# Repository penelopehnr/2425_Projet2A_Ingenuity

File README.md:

# 2425_Projet2A_Ingenuity

**Students :**

- Pénélope HENNER - penelope.henner@ensea.fr
- Kavin DUGARD - kevin.dugard@ensea.fr 
- Elio FLANDIN - elio.flandin@ensea.fr
- Joel COLASO - joel.colaso@ensea.fr

## Project background:

Mars 2020 is a space mission to deploy the Perseverance rover on the Martian surface to study its surface and collect soil samples. It is the first of a series of three missions whose ultimate aim is to return these samples to Earth for analysis.

Ingenuity is a small helicopter developed by NASA, the US space agency. It is being used experimentally on the surface of Mars during the Mars 2020 mission. The helicopter is on board the Perseverance rover.

On April 19, 2021, for the first time in the history of the space age, a spacecraft makes a powered flight through the tenuous atmosphere of another planet. Ingenuity's objective is optical reconnaissance of the terrain, with the helicopter taking numerous aerial photos used by the pilots of the Perseverance astromobile to identify obstacles and promising sites (taking rock samples from the Martian soil).

Ingenuity is a 1.8 kg helicopter with 2 coaxial counter-rotating rotors. It draws its energy from 6 lithium-ion batteries recharged by solar cells. Its navigation system enables it to follow a pre-programmed route without human intervention. Its only payload is a camera.

The mission recently came to an end (January 18, 2024) when a blade broke during the 72nd flight.

Ingenuity has opened up new prospects for Mars exploration. NASA and ESA, as part of their Mars sample return mission, are now including 2 similar helicopters to collect the tubes containing the Martian samples deposited by the Perseverance astromobile in the event of its failure.

 Our project is therefore to try to build the Ingenuity module in miniature. In other words, we want to create a vehicle that can move through the air and take a photo of what's going on below.

 [Learn more about the Mars 2020 mission](Ingenuity%20March%202020.md)

## Our project

Our project is to try and make this helicopter in miniature mode. In other words, we want to create a vehicle that can move through the air and take a photo of what's happening below. To do this, we'll have a total of 10 sessions in which we'll have to mix PCBs, coding, soldering and so on.

## Project architecture

## Description of repo structure:

``````
.
├── Assets/            # Project images (drone, PCB)
├── Datasheets/        # Component datasheets
├── Hardware/          # Architecture diagrams, KiCad (PCB) files and 3D files
├── Software/          # Embedded code (STM32) + Python code + TOF module
├── README.md          # Main project documentation
├── Ingenuity March 2020.md  # Background on the Mars 2020 mission

``````

In the **Assets** folder, you will find pictures of the drone and the assembled PCB.

The **Datasheets** folder contains documentation for all the components we used throughout the project.

The **Hardware** folder includes all the KiCad files needed to reproduce our custom PCB, along with the Bill of Materials (BOM) listing all components, their references, and specifications. You will also find files for 3D printing and laser cutting the various structural parts of the drone.

The **Software** folder contains:
- The **Python code** used to build the graphical user interface (GUI) on the PC to communicate with the Raspberry Pi (`Client_GUI.py`).
- The **Python code** running on the Raspberry Pi, which handles communication with the microcontroller and takes pictures (`server.py`).
- The **TOF code** (developed with STM32CubeIDE), which is responsible for sending the drone’s altitude using a Time-of-Flight sensor.
- The **C code** (also under STM32CubeIDE) in `Ingenuity_2A`, running on the STM32 microcontroller, which receives commands from the Raspberry Pi and manages the components such as motors, TOF sensor, etc.

## Environments used: 

### Machines Used
- **PC (Windows/macOS/Linux)**: Used for development (STM32CubeIDE, Python, OnShape, etc.).
- **Function Generator (GBF)**: Used to simulate control signals during motor testing.
- **Laser Cutter (FabLab)**: Used to cut the wooden drone structure.

### Hardware
- **Raspberry Pi Zero**: A single-board computer used for image capture, PCB interfacing, and running Python scripts.
- **STM32L412KBT6**: Main microcontroller used on the custom PCB.
- **VL53L1X**: Time-of-Flight (ToF) distance sensor.
- **ESC (Electronic Speed Controllers)**: To control brushless motors.
- **Brushless Motors**: Used to generate drone thrust.
- **LDO BU33TD3WG**: Low-dropout voltage regulator.
- **Buck Converter 17395xx36**: DC-DC converter used to step down voltage.
- **MOSFETs**: Used for power switching and motor control.
- **Camera (connected to Raspberry Pi)**: Captures aerial images.

### Software
#### Embedded Development
- **STM32CubeIDE**: Used to write, compile, and flash firmware to the microcontroller.
- **STM32 HAL Drivers**: Low-level drivers for managing STM32 peripherals.

#### Electronic Design
- **KiCad**: Used for circuit schematic design, PCB layout, and Gerber/BOM export.
- **OnShape**: Used for 3D modeling of the drone structure.

#### Python Development
- **Python 3**: Used for drone communication scripts and the graphical user interface (GUI).
- **Tkinter / PyQt**: Used to build the GUI interface.
- **Pygame / Other sound libraries**: For playing feedback sounds (from the `sounds/` folder).
- **Flask / TCP Sockets**: For communication between the GUI and the drone.

## Precision on the TOF VL53L1X

Start by copying the ```VL53L1X_ULD_API``` in your project. You want to configure the paths in your IDE (eg. in STM32CubeIDE : ```Project > Properties``` then ```C/C++ General > Paths and Symbols```).

Source (code and explanations): https://github.com/lfiack/tof_VL53L1X-SATEL/blob/main/README.md

## Precise notice of our project 

[Mini-Ingenuity notice](Mini-Ingenuity_notice.md)

## Logbook

[Logbook](LogBook.md)

## Picture of Mini-Ingenuity

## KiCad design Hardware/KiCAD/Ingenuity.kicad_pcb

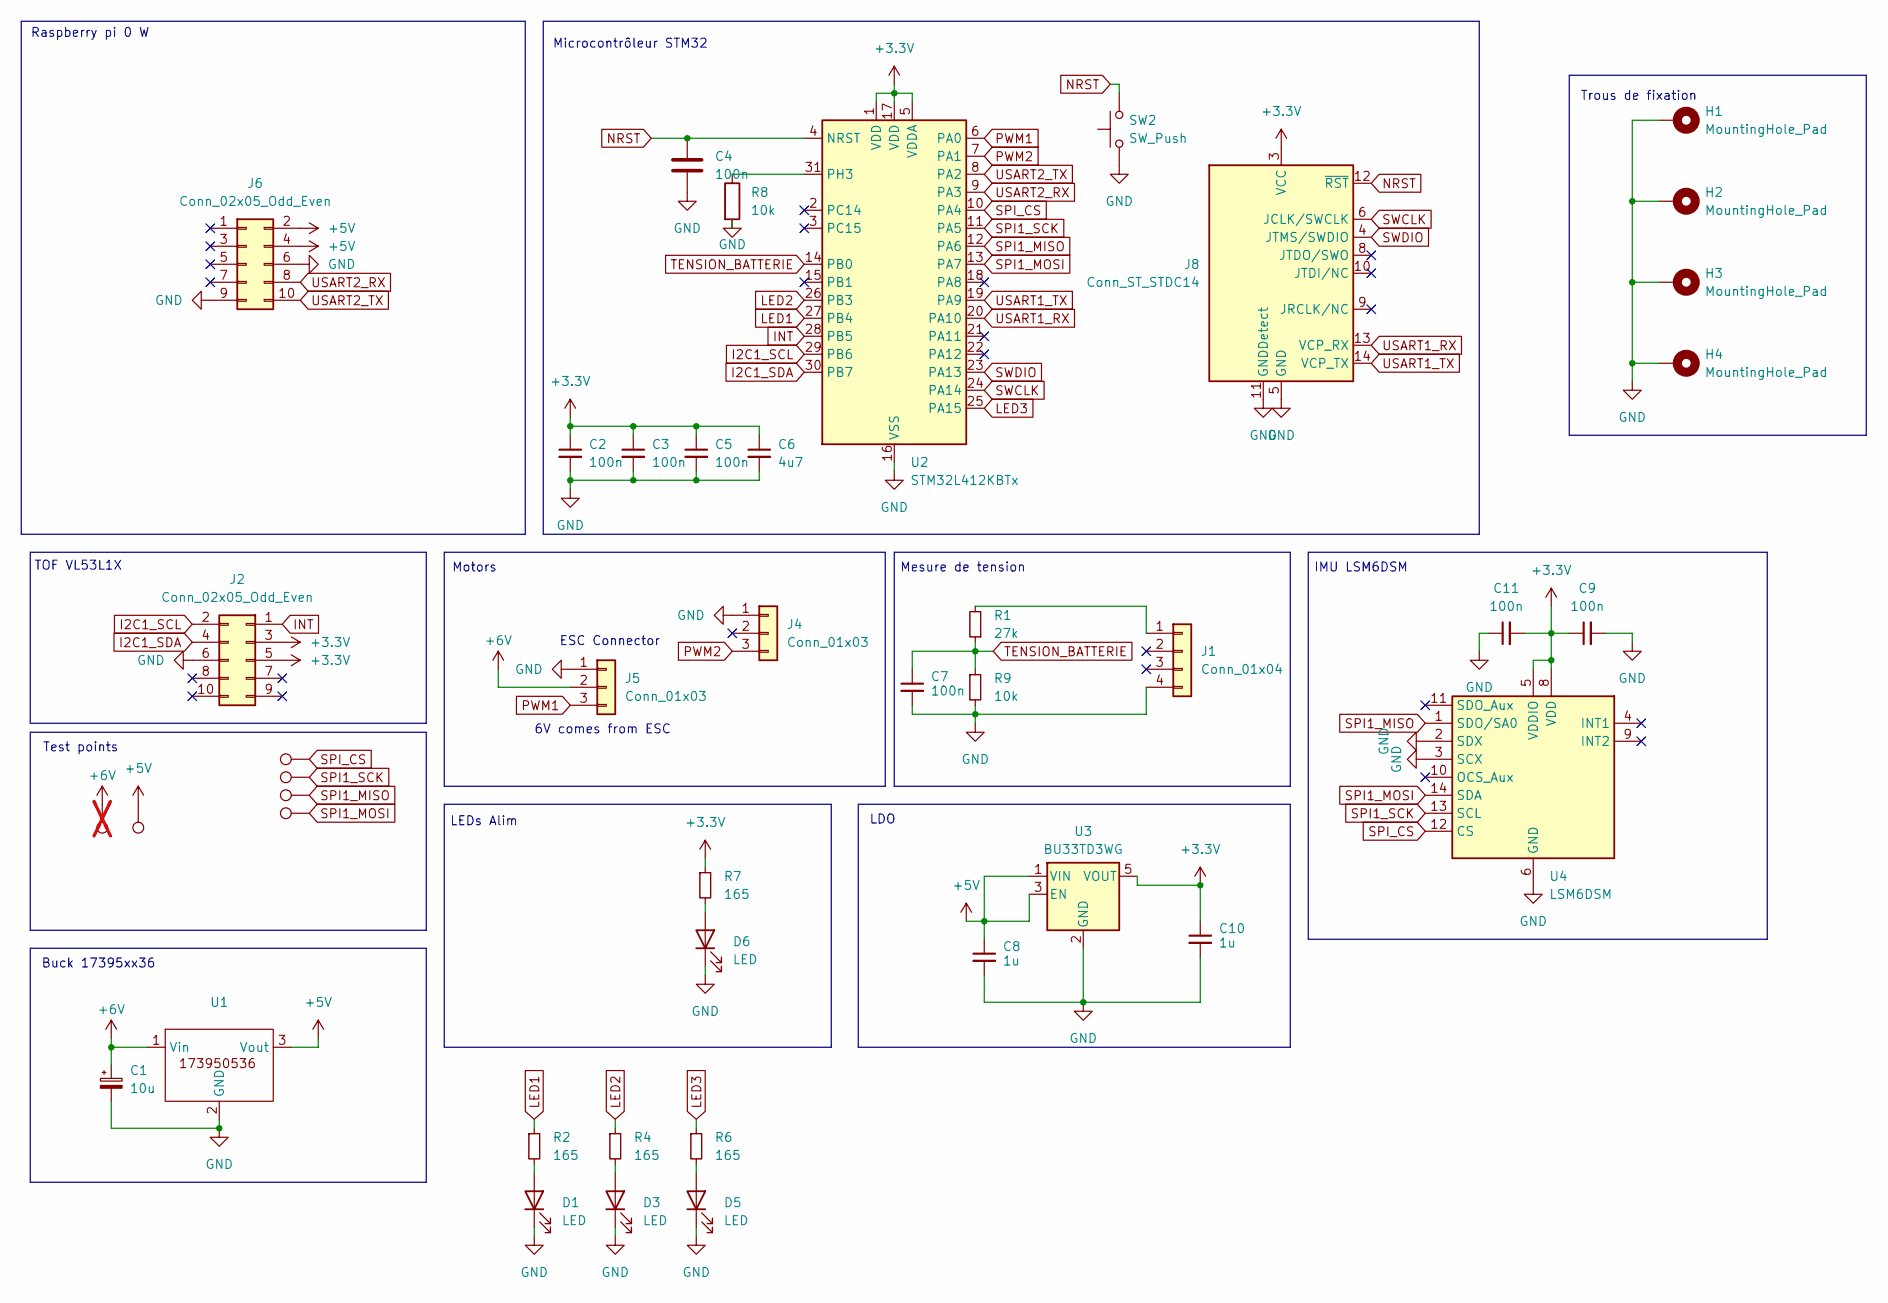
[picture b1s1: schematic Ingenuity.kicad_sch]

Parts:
C1: 10u; C_0603_1608Metric
C2, C3, C4, C5, C7, C9, C11: 100n; C_0402_1005Metric
C6: 4u7; C_0402_1005Metric
C8, C10: 1u; C_0402_1005Metric
D1, D3, D5, D6: LED; LED_0603_1608Metric
H1, H2, H3, H4: MountingHole_Pad; MountingHole_2.7mm_M2.5_DIN965_Pad
J1: Conn_01x04; JST_XH_B4B-XH-A_1x04_P2.50mm_Vertical
J2, J6: Conn_02x05_Odd_Even; PinHeader_2x05_P2.54mm_Vertical
J4, J5: Conn_01x03; JST_XH_B3B-XH-A_1x03_P2.50mm_Vertical
J8: Conn_ST_STDC14; PinHeader_2x07_P1.27mm_Vertical_SMD
R1: 27k; R_0402_1005Metric
R2, R4, R6, R7: 165; R_0402_1005Metric
R8, R9: 10k; R_0402_1005Metric
SW2: SW_Push; SW_Push_1P1T_NO_6x6mm_H9.5mm
TP1: TestPoint; TestPoint_Pad_D1.5mm; not fitted
TP2, TP3, TP4, TP5, TP6: TestPoint; TestPoint_Pad_D1.5mm
U1: Buck_ing; MPN 173950536
U2: STM32L412KBTx; LQFP-32_7x7mm_P0.8mm; MPN STM32L412KBT6
U3: BU33TD3WG; SOT-23-5; MPN BU33TD3WG-TR
U4: LSM6DSM; LGA-14_3x2.5mm_P0.5mm_LayoutBorder3x4y; MPN LSM6DSMTR

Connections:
+3.3V: C2.1, C3.1, C5.1, C6.1, C9.1, C10.1, C11.2, J2.3, J2.5, J8.3 (VCC), R7.1, U2.1 (VDD), U2.5 (VDDA), U2.17 (VDD), U3.5 (VOUT), U4.5 (VDDIO), U4.8 (VDD)
+5V: C8.1, J6.1, J6.2, J6.4, TP2.1, U1.3 (Vout), U3.1 (VIN), U3.3 (EN)
+6V: C1.1, J5.2, TP1.1, U1.1 (Vin)
GND: C1.2, C2.2, C3.2, C4.2, C5.2, C6.2, C7.2, C8.2, C9.2, C10.2, C11.1, D1.1 (K), D3.1 (K), D5.1 (K), D6.1 (K), H1.1, H2.1, H3.1, H4.1, J1.4, J2.6, J4.1, J5.1, J6.6, J6.9, J8.5 (GND), J8.7 (GND), J8.11 (GNDDetect), R8.2, R9.2, SW2.1, U1.2 (GND), U2.16 (VSS), U2.32 (VSS), U3.2 (GND), U4.2 (SDX), U4.3 (SCX), U4.6 (GND), U4.7 (GND)
I2C1_SCL: J2.2, U2.29 (PB6)
I2C1_SDA: J2.4, U2.30 (PB7)
INT: J2.1, U2.28 (PB5)
LED1: R2.1, U2.27 (PB4)
LED2: R4.1, U2.26 (PB3)
LED3: R6.1, U2.25 (PA15)
NRST: C4.1, J8.12 (~RST), SW2.2, U2.4 (NRST)
unnamed: D1.2 (A), R2.2
unnamed: D3.2 (A), R4.2
unnamed: D5.2 (A), R6.2
unnamed: D6.2 (A), R7.2
unnamed: J1.1, R1.2
unnamed: R8.1, U2.31 (PH3)
PWM1: J5.3, U2.6 (PA0)
PWM2: J4.3, U2.7 (PA1)
SPI1_MISO: TP5.1, U2.12 (PA6), U4.1 (SDO/SA0)
SPI1_MOSI: TP6.1, U2.13 (PA7), U4.14 (SDA)
SPI1_SCK: TP4.1, U2.11 (PA5), U4.13 (SCL)
SPI_CS: TP3.1, U2.10 (PA4), U4.12 (CS)
SWCLK: J8.6 (JCLK/SWCLK), U2.24 (PA14)
SWDIO: J8.4 (JTMS/SWDIO), U2.23 (PA13)
TENSION_BATTERIE: C7.1, R1.1, R9.1, U2.14 (PB0)
USART1_RX: J8.13 (VCP_RX), U2.20 (PA10)
USART1_TX: J8.14 (VCP_TX), U2.19 (PA9)
USART2_RX: J6.8, U2.9 (PA3)
USART2_TX: J6.10, U2.8 (PA2)

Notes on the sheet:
Trous de fixation
Mesure de tension
Motors
LDO
6V comes from ESC
Buck 17395xx36
Raspberry pi 0 W
IMU LSM6DSM
Test points
ESC Connector
LEDs Alim
Microcontrôleur STM32
TOF VL53L1X

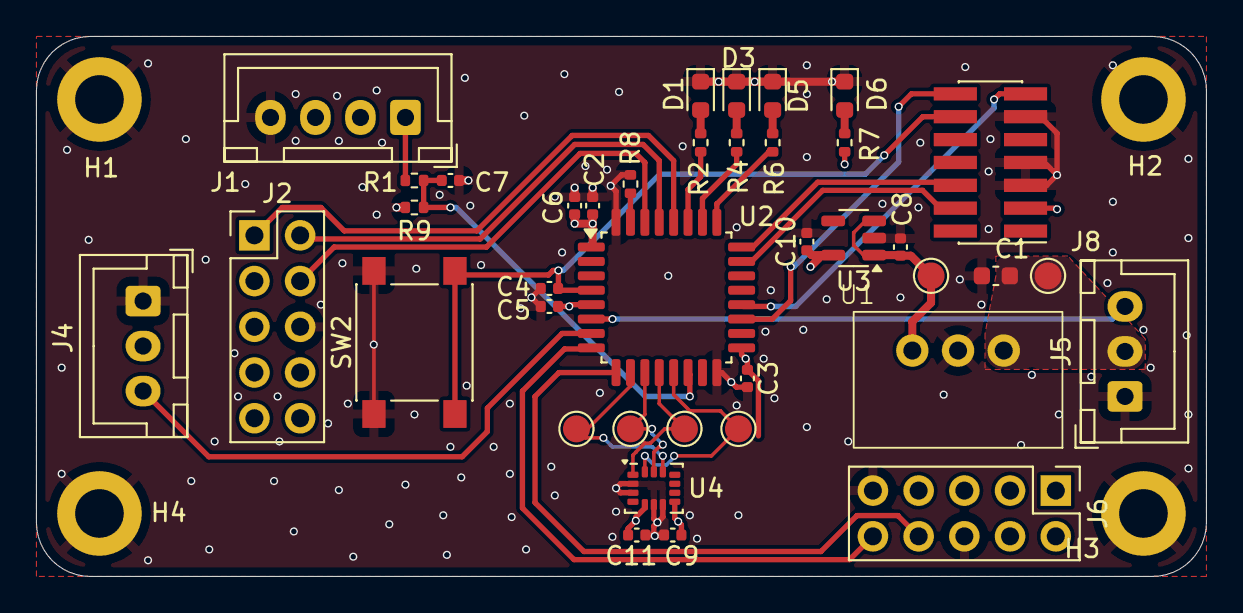
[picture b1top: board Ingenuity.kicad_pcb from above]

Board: 4 copper layers, 65.0 x 30.0 mm, 43 parts (0 on the bottom side), 30 nets.

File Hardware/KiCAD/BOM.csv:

Reference	Value	Datasheet	Footprint	Qty	DNP
C1	10u	~	Capacitor_SMD:C_0603_1608Metric	1	
C2,C3,C4,C5,C7,C9,C11	100n	~	Capacitor_SMD:C_0402_1005Metric	7	
C6	4u7	~	Capacitor_SMD:C_0402_1005Metric	1	
C8,C10	1u	~	Capacitor_SMD:C_0402_1005Metric	2	
D1,D3,D5,D6	LED	~	LED_SMD:LED_0603_1608Metric	4	
H1,H2,H3,H4	MountingHole_Pad	~	MountingHole:MountingHole_2.7mm_M2.5_DIN965_Pad	4	
J1	Conn_01x04	~	Connector_JST:JST_XH_B4B-XH-A_1x04_P2.50mm_Vertical	1	
J2	Conn_02x05_Odd_Even	~	Connector_PinHeader_2.54mm:PinHeader_2x05_P2.54mm_Vertical	1	
J3	Conn_02x20_Odd_Even	~	Connector_PinHeader_2.54mm:PinHeader_2x20_P2.54mm_Vertical	1	
J4,J5	Conn_01x03	~	Connector_JST:JST_XH_B3B-XH-A_1x03_P2.50mm_Vertical	2	
J8	Conn_ST_STDC14	https://www.st.com/content/ccc/resource/technical/document/u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	Connector_PinHeader_1.27mm:PinHeader_2x07_P1.27mm_Vertical_SMD	1	
R1	27k	~	Resistor_SMD:R_0402_1005Metric	1	
R2,R4,R6,R7	165	~	Resistor_SMD:R_0402_1005Metric	4	
R8,R9	10k	~	Resistor_SMD:R_0402_1005Metric	2	
SW2	SW_Push	~	Button_Switch_SMD:SW_Push_1P1T_NO_6x6mm_H9.5mm	1	
TP1,TP2,TP3,TP4,TP5,TP6	TestPoint	~	TestPoint:TestPoint_Pad_D1.5mm	6	
U1	~		myemp:Buck_ing	1	
U2	STM32L412KBTx	https://www.st.com/resource/en/datasheet/stm32l412kb.pdf	Package_QFP:LQFP-32_7x7mm_P0.8mm	1	
U3	BU33...	https://ww1.microchip.com/downloads/aemDocuments/documents/O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	Package_TO_SOT_SMD:SOT-23-5	1	
U4	LSM6DSM	https://www.st.com/resource/en/datasheet/lsm6dsm.pdf	Package_LGA:LGA-14_3x2.5mm_P0.5mm_LayoutBorder3x4y	1

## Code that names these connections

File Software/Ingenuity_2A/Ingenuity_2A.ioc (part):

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Mcu.Name=STM32L412KBTx
Mcu.Package=LQFP32
Mcu.UserName=STM32L412KBTx
PA0-CK_IN.Signal=S_TIM2_CH1
PA1.Signal=S_TIM2_CH2
PA10.Mode=Asynchronous
PA10.Signal=USART1_RX
PA13\ (JTMS/SWDIO).Mode=Serial_Wire
PA13\ (JTMS/SWDIO).Signal=SYS_JTMS-SWDIO
PA14\ (JTCK/SWCLK).Mode=Serial_Wire
PA14\ (JTCK/SWCLK).Signal=SYS_JTCK-SWCLK
PA15\ (JTDI).GPIOParameters=GPIO_Label
PA15\ (JTDI).GPIO_Label=LED3
PA15\ (JTDI).Signal=GPIO_Output
PA2.Mode=Asynchronous
PA2.Signal=USART2_TX
PA3.Mode=Asynchronous
PA3.Signal=USART2_RX
PA4.Mode=NSS_Signal_Hard_Output
PA4.Signal=SPI1_NSS
PA5.Mode=Full_Duplex_Master
PA5.Signal=SPI1_SCK
PA6.Mode=Full_Duplex_Master
PA6.Signal=SPI1_MISO
PA7.Mode=Full_Duplex_Master
PA7.Signal=SPI1_MOSI
PA9.Mode=Asynchronous
PA9.Signal=USART1_TX
PB0.GPIOParameters=GPIO_Label
PB0.GPIO_Label=BATTERIE
PB0.Signal=ADCx_IN15
PB3\ (JTDO/TRACESWO).GPIOParameters=GPIO_Label
PB3\ (JTDO/TRACESWO).GPIO_Label=LED2
PB3\ (JTDO/TRACESWO).Signal=GPIO_Output
PB4\ (NJTRST).GPIOParameters=GPIO_Label
PB4\ (NJTRST).GPIO_Label=LED1
PB4\ (NJTRST).Signal=GPIO_Output
PB5.GPIOParameters=GPIO_Label
PB5.GPIO_Label=TOF_INT
PB5.Signal=GPXTI5
PB6.Mode=I2C
PB6.Signal=I2C1_SCL
PB7.Mode=I2C
PB7.Signal=I2C1_SDA
RCC.HSE_VALUE=8000000
board=custom

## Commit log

2024-09-17 README modif
2024-09-17 tree
2024-09-17 schéma archi V1
2024-09-17 datasheet MOSFET
2024-09-17 output
2024-09-24 schéma archi V2
2024-09-24 about Ingenuity
2024-09-24 schema archi V3
2024-09-24 datasheet added
2024-09-24 datasheet added buck
2024-10-08 schéma d'architecture V4
2024-10-08 KiCAD
2024-10-08 Project STM32
2024-10-08 README tree
2024-10-08 Python
2024-10-08 changement kicad
2024-10-22 Updated Python codes
2024-10-22 Create Notice
2024-10-22 Update Notice
2024-10-22 Update and rename Notice.md to Notice
2024-10-22 Rename Notice to Notice.md
2024-10-22 Notice added
2024-10-22 Updated Notice
2024-10-23 Refresh name
2024-11-11 Translation FR->EN
2024-11-12 update Python code
2024-11-12 maj BOM-MPN
2024-11-19 update MPN BOMv3
2024-12-10 assets
2024-12-10 mini ingenuity picture
2024-12-10 pcb picture
2024-12-19 File type changed
2024-12-19 Readable image
2024-12-19 File name translated
2024-12-20 Updated code with main (containing 3 tests), motor.c, decodeInstruction.c, updated timer configuration PWM
2025-01-14 Update README (logbook)
2025-01-14 GUI in Python learning
2025-01-21 update RasPi connector
2025-01-23 Python GUI update
2025-01-28 Kicad update
2025-01-28 Update README (session 11)
2025-01-28 update kicad reduction taille pcb
2025-01-28 end kicad V2
2025-01-29 change pcb dimensions and fix errors, ready for fab
2025-01-30 GUI updated
2025-02-04 KiCad PCB V2
2025-02-04 Update README.md (Session 13)
2025-02-04 update KiCad
2025-02-05 Client_GUI update
2025-02-11 update BOM
2025-03-03 modif KiCad
2025-03-04 Update README.md Session 15
2025-03-25 readme
2025-03-25 .DS_Store removed
2025-03-25 work on the git
2025-03-25 readme ingenuity and pictures
2025-03-25 "d fils
2025-03-25 3D files
2025-03-25 logbook
2025-03-25 notice
2025-03-25 add 3D design
2025-03-25 wood structure
2025-03-25 Update LogBook (session 16, 17 and 18)
2025-03-27 Update python codes
2025-03-27 Useless files deleted
2025-03-27 Files name translated
2025-03-27 General notice updated - Python part
2025-04-16 pictures + readme
2025-04-17 Update LogBook (Session 19)
2025-04-17 3D design added
2025-04-17 translation
2025-04-27 Updated Mini-Ingenuity_notice.md software section
2025-04-28 Updated STM32 code
